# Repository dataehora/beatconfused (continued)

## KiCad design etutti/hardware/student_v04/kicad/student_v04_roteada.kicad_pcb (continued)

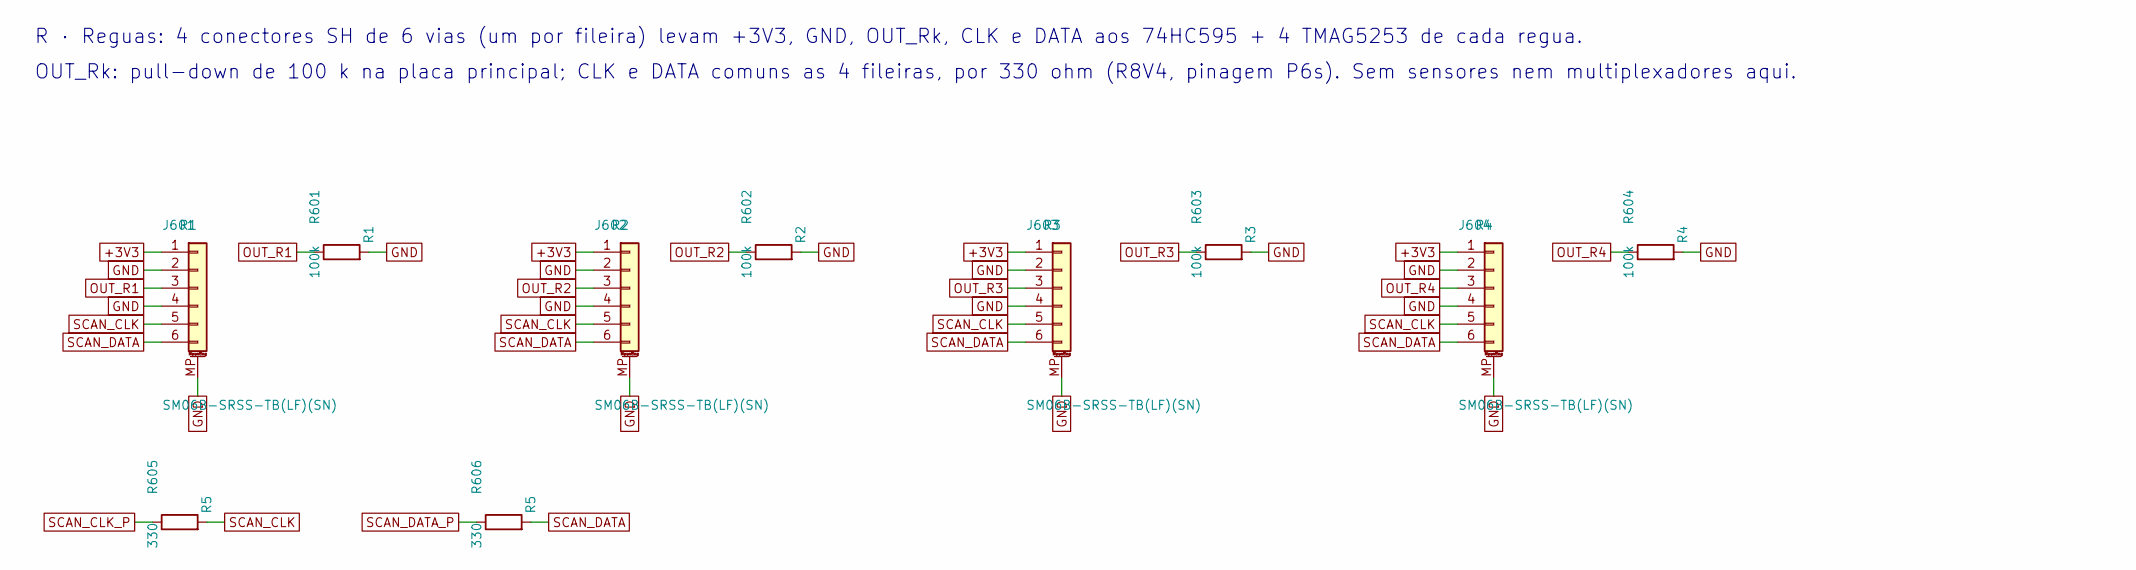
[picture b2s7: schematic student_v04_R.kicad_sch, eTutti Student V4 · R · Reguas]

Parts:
J601, J602, J603, J604: SM06B-SRSS-TB(LF)(SN); JST_SH_SM06B-SRSS-TB_1x06-1MP_P1.00mm_Horizontal; LCSC C160405
R601, R602, R603, R604: 100k; R_0402_1005Metric; LCSC C25741
R605, R606: 330; R_0402_1005Metric; LCSC C25104

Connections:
+3V3: J601.1, J602.1, J603.1, J604.1; also elsewhere on the board
GND: J601.2, J601.4, J601.MP (MountPin), J602.2, J602.4, J602.MP (MountPin), J603.2, J603.4, J603.MP (MountPin), J604.2, J604.4, J604.MP (MountPin), R601.2, R602.2, R603.2, R604.2; also elsewhere on the board
OUT_R1: J601.3, R601.1; also elsewhere on the board
OUT_R2: J602.3, R602.1; also elsewhere on the board
OUT_R3: J603.3, R603.1; also elsewhere on the board
OUT_R4: J604.3, R604.1; also elsewhere on the board
SCAN_CLK: J601.5, J602.5, J603.5, J604.5, R605.2
SCAN_CLK_P: R605.1; also elsewhere on the board
SCAN_DATA: J601.6, J602.6, J603.6, J604.6, R606.2
SCAN_DATA_P: R606.1; also elsewhere on the board

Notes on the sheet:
R · Reguas: 4 conectores SH de 6 vias (um por fileira) levam +3V3, GND, OUT_Rk, CLK e DATA aos 74HC595 + 4 TMAG5253 de cada regua.
OUT_Rk: pull-down de 100 k na placa principal; CLK e DATA comuns as 4 fileiras, por 330 ohm (R8V4, pinagem P6s). Sem sensores nem multiplexadores aqui.

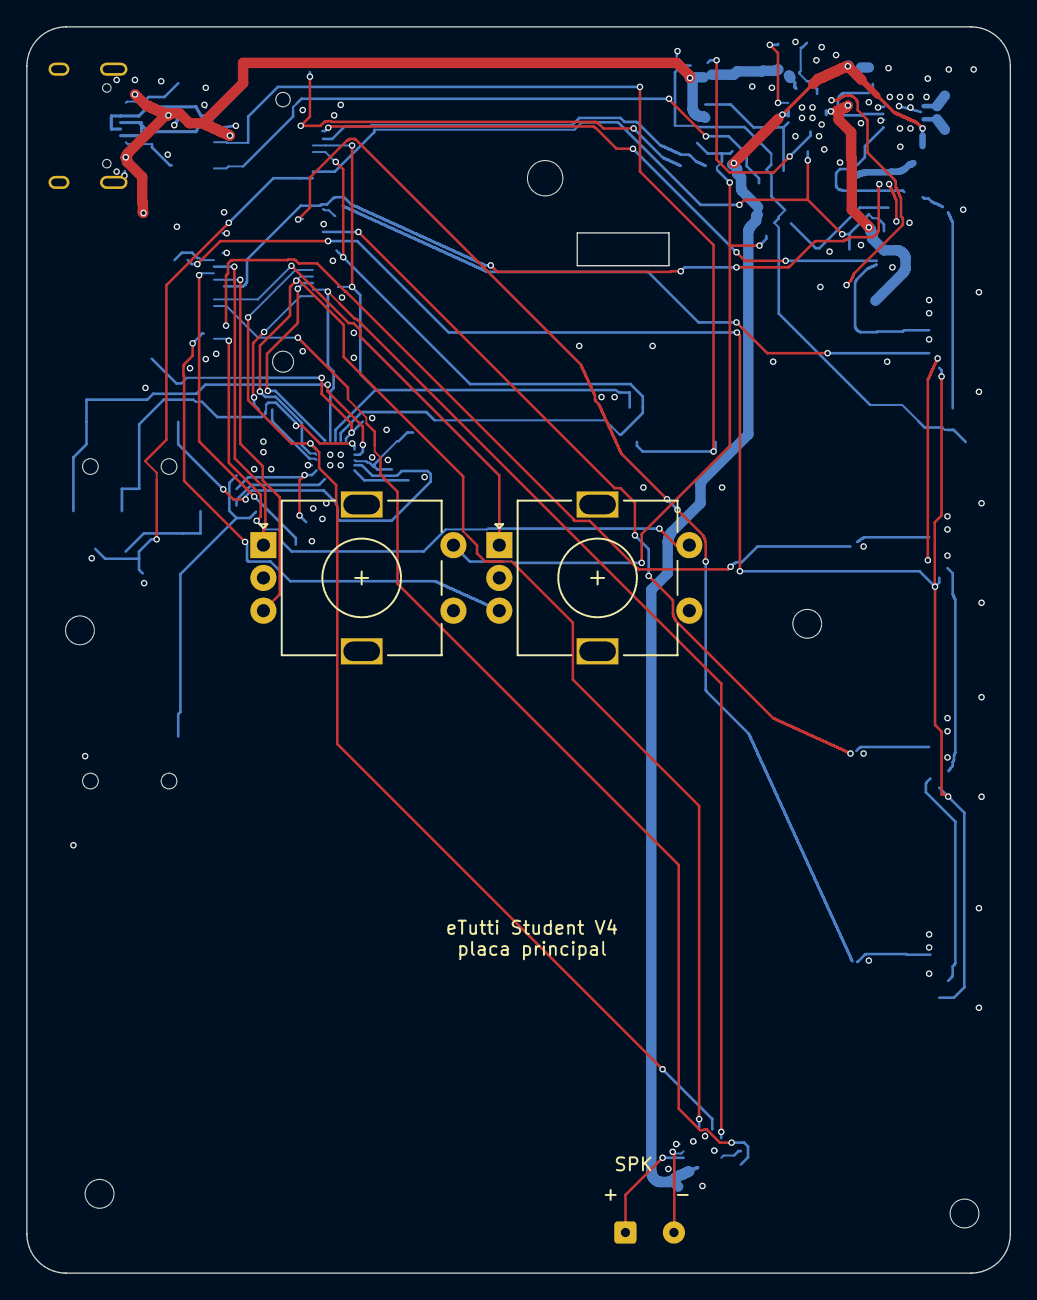
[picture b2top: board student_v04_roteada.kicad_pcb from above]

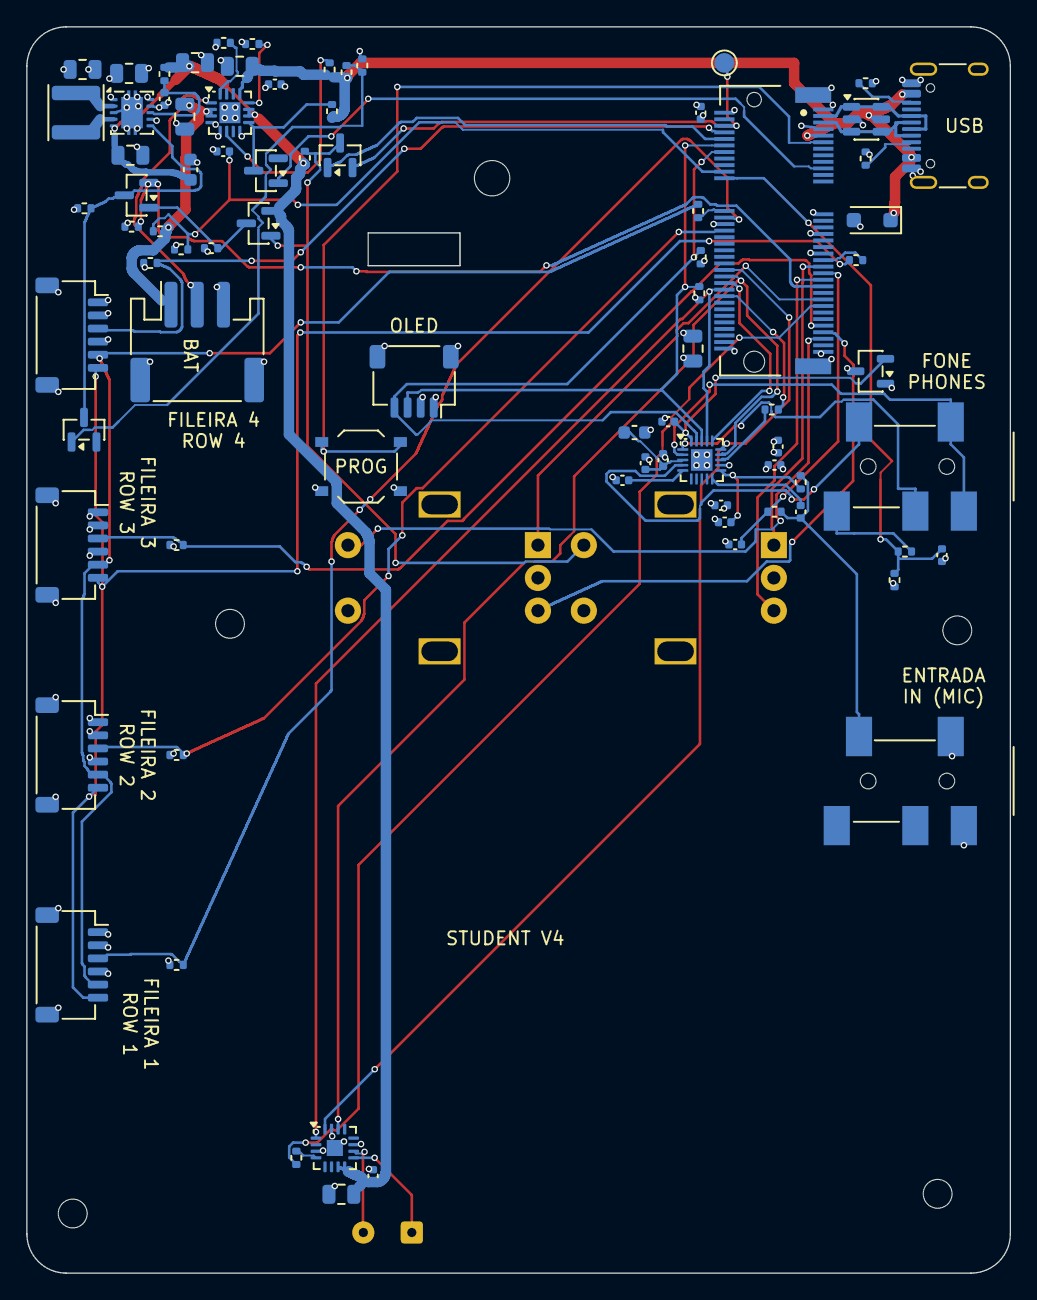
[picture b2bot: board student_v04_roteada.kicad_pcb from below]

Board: 4 copper layers, 75.0 x 95.1 mm, 88 parts (80 on the bottom side), 64 nets.

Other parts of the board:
H1, H2, H3, H4: MountingHole_2.2mm_M2
H101: MountingHole_2.7mm_M2.5

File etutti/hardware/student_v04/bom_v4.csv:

lcsc,valor,classe_jlc,qtd,referencias,preco_unit_usd
C15850,10uF,Basic,8,C101 C201 C202 C203 C206 C207 C208 C501,0.0311
C1525,100nF,Basic,11,C102 C204 C205 C209 C302 C304 C305 C307 C308 C311 C502,0.0025
C19702,10uF,Basic,1,C210,0.0167
C12530,2.2uF,Basic,3,C301 C303 C306,0.005
C52923,1uF,Basic,1,C309,0.0055
C151296,SMF5.0A,Extended,1,D201,0.1144
C68978,BAV70,Basic,4,D202 D203 D206 D205,0.0152
C1002,600R@100MHz,Basic,1,FB301,0.0105
C48985906,91302-42-067RCE,Extended,1,J101,1.2304
C165948,TYPE-C-31-M-12,Extended,1,J201,0.1869
C265101,S3B-PH-SM4-TB,Extended,1,J202,0.2641
C49284723,PJ-327A,Extended,2,J301 J302,0.2194
C160404,SM04B-SRSS-TB(LF)(SN),Extended,1,J401,0.2147
C160405,SM06B-SRSS-TB(LF)(SN),Extended,4,J601 J602 J603 J604,0.8966
C167825,2.2uH,Extended,1,L201,0.0516
C15127,AO3401A,Basic,1,Q203,0.082
C25076,100,Basic,2,R105 R216,0.0011
C25905,5.1k,Basic,2,R201 R202,0.0014
C25879,2.2k,Basic,3,R203 R301 R302,0.0011
C25867,1.5k,Basic,1,R204,0.0029
C25744,10k,Basic,2,R205 R214,0.001
C25741,100k,Basic,11,R206 R210 R211 R213 R215 R303 R306 R601 R602 R603 R604,0.0009
C26083,1M,Basic,5,R208 R209 R212 R304 R501,0.001
C17168,0,Basic,1,R305,0.0012
C25104,330,Basic,2,R605 R606,0.0011
C318884,Program,Basic,1,SW403,0.0212
C7519,USBLC6-2SC6,Extended,1,U201,0.1561
C54313,BQ24074RGTR,Extended,1,U202,2.1646
C28060,TPS63001DRCR,Extended,1,U204,1.6247
C2651833,SGTL5000XNLA3,Extended,1,U301,9.5073
C347373,XC6206P182MR,Extended,1,U302,0.021
C910544,MAX98357AETE+T,Extended,1,U501,1.2451

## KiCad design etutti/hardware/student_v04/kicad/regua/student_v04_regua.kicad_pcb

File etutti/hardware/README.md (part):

# eTuttino — PCB design (Hall-effect, velocity-sensitive)

A 44-key chromatic button-accordion controller (C-griff, G3–E6).

- **Keys:** Gateron magnetic (Hall-effect) switches, MX-compatible.
- **Sensing:** a TI DRV5056A3 linear Hall sensor under every key, so the
  firmware knows how far down each key is, and from how fast it went
  down, the note's velocity.
- **Brain:** a Teensy 4.0 with the PJRC Audio Adaptor Board Rev D stacked
  on it.

The firmware is in [`../firmware`](../firmware), the web page is
[beatconfused.com/etutti](https://beatconfused.com/etutti/), and the case
(Seixo / Madeira, SPEC v9; shape frozen since v7) is in [`case/`](case/).

> **Board v0.7 (this one) is made for the SPEC v7–v9 case.** The keys sit
> on the case's hexagonal grid (18.5 mm pitch), and the board takes the
> case's inner outline. The assembly and user manuals in
> [`../manuais`](../manuais/) describe this board, the case and the
> controls board; their pictures come from
> [`manual3d/`](manual3d/) (Blender). Nothing has been built
> yet: only the firmware has run on a real Teensy + Audio Board.

## Ordering (ready to upload)

Generated, routed and checked: KiCad DRC 0 errors, 0 warnings,
0 unconnected; firmware cross-check 44/44.

| File | Upload it as |
| --- | --- |
| [`fab/etuttino_gerbers.zip`](fab/etuttino_gerbers.zip) | **the PCB**: Gerbers + drill files. 2 layers, FR-4, **1.2 mm**, shaped outline (328 × 97 mm bounding box) |
| [`fab/etuttino_bom.csv`](fab/etuttino_bom.csv) + [`fab/etuttino_cpl_bottom.csv`](fab/etuttino_cpl_bottom.csv) | **assembly** (JLCPCB PCBA, *Bottom Side*): every SMD part is on the back |
| [`fab/etuttino_plate_gerbers.zip`](fab/etuttino_plate_gerbers.zip) | **the switch plate**: a copper-less **1.6 mm** FR-4 board with the 14 mm cutouts, cut to the case's plate outline (the case is drawn for 1.6 since SPEC v8) |
| [`fab/etuttino_controls_gerbers.zip`](fab/etuttino_controls_gerbers.zip) | **the controls board**: 2 layers, FR-4 1.6 mm, 41.5 × 25.5 mm, all through-hole (see below) |
| [`case/out/`](case/out/) | **the case** (STEP + STL) and the button caps; see [`case/README.md`](case/README.md) |

The BOM has LCSC numbers for the JLCPCB basic parts. Match the two TI parts
(`DRV5056A3QDBZR`, `CD74HC4067M96`) by manufacturer part number in
JLCPCB's BOM tool. Check every part's rotation in the placement preview
before paying.

## Why the sensors are on the back

The DRV5056 is unipolar: its output only rises when a **south** pole faces
its marked (top) side. Gateron's magnetic switches have the magnet's
**north** pole facing down, so a sensor on the front, facing up, would read
nothing.

On the back, the sensor faces away from the switch. The field reaches it
through the board from behind, and the sensor reads that as positive. A
1.2 mm board keeps the sensor as close to the magnet as that allows.

The A3 variant (30 mV/mT at 3.3 V, about 80 mT before saturation) leaves
headroom against Gateron's ~10 mT at rest and ~90 mT bottomed out. The A4
also works.

## Source files and regenerating

| File | What it is |
| --- | --- |
| [`case/pcb_envelope.py`](case/pcb_envelope.py) → `case/out/pcb_envelope.json` | the room the case leaves for the board: outline (notched round the case's screw bosses), plate outline, bottom-plate pillars, height levels, key centres, the stack's and J3's places. Run with the CadQuery venv (see `case/README.md`) |
| [`generate.py`](generate.py) | reads that envelope. Single source of the key layout and of the sensor → multiplexer map (plain Python 3). Prints the `KEY_INPUT` table for the firmware |
| [`build_pcb.py`](build_pcb.py) | builds and **routes** the KiCad board inside that outline, runs DRC, checks it against the firmware, exports everything in `fab/` |
| [`controls_pcb.py`](controls_pcb.py) | the controls board: places, routes (the same router), DRCs and exports it |
| [`mechanics.py`](mechanics.py) | how far the board bends under a key press on the case's pillars (KiCad's Python, numpy) |
| [`manual3d/`](manual3d/) | the assembly manual's pictures: photo-like renders and numbered line drawings of every step, made in Blender from the case STLs, both KiCad boards (`kicad-cli` GLB) and a library of datasheet-sized parts (`parts.py`). `build.py` runs it all; the visual standard and the balloon numbers are in [`manual3d/STYLE.md`](manual3d/STYLE.md) |
| [`etuttino.pretty/`](etuttino.pretty) | footprint library: `Gateron_Magnetic_MX_1u` (two 1.75 mm peg holes, no centre post, no pins), origin at the switch centre |
| [`kicad/etuttino.kicad_pcb`](kicad/etuttino.kicad_pcb), [`kicad/etuttino_plate.kicad_pcb`](kicad/etuttino_plate.kicad_pcb) | the routed board and the plate |
| `build/etuttino_pcb_preview.svg`, `build/etuttino_keys.csv`, `build/etuttino_plate.dxf` | preview; each key's switch, sensor, multiplexer channel, Teensy pin, note and X/Y; the plate as DXF (for aluminium) |

After a case change, rebuild in this order:

```bash
C:/Users/julia/.venvs/cadquery/Scripts/python.exe case/case.py
C:/Users/julia/.venvs/cadquery/Scripts/python.exe case/pcb_envelope.py
python generate.py
"C:/Program Files/KiCad/10.0/bin/python.exe" build_pcb.py
"C:/Program Files/KiCad/10.0/bin/python.exe" mechanics.py
```

Each routing attempt takes about four minutes. The router is greedy: if
a net can't be routed, the script starts again with that net first, up to
20 times. `DEFAULT_ROUTE_FIRST` keeps the order that worked
(`OUT_U41,OUT_U42,GND,LED_R,LED_G_DRV,OUT_U34` for v0.6 and v0.7).

`build_pcb.py` exits with an error if any of these happens:

- DRC finds a problem.
- Anything is left unconnected.
- A part on the back sits over one of the bottom plate's pillars.
- A key doesn't reach the multiplexer channel and Teensy pin that the
  firmware's tables give.

It writes the routed channels into the sketch's `KEY_INPUT`.

## Layout

Chromatic accordion, C-griff, on a **hexagonal grid**: every button is
**18.5 mm** from its six neighbours, and the rows are 18.5 × cos 30° =
**16.02 mm** apart.

- Each key along a row is a **minor third (3 semitones)** above the
  previous one. A diagonal step to the next row is **one semitone**.
- Row 4 repeats row 1's notes from A3 to C6, on row 2's columns.
- **Row 1 is nearest the player.** It is at the front edge, which is the
  bottom of KiCad's top view.
- The same switches also play **B-griff**: the web page's C/B-griff
  switch sends CC 24, and the firmware swaps rows 1 and 3. The PCB does
  not change.

| Row | Keys | Notes | y (mm) |
| --- | --- | --- | --- |
| 1 | 11 | A3 C4 D♯4 F♯4 A4 C5 D♯5 F♯5 A5 C6 D♯6 | 74.03 |
| 2 | 12 | G3 A♯3 C♯4 E4 G4 A♯4 C♯5 E5 G5 A♯5 C♯6 E6 | 58.01 |
| 3 | 11 | G♯3 B3 D4 F4 G♯4 B4 D5 F5 G♯5 B5 D6 | 41.99 |
| 4 | 10 | A3 C4 D♯4 F♯4 A4 C5 D♯5 F♯5 A5 C6 | 25.97 |

**Coordinates** are the case SPEC's. x is measured from the case's left
face, y towards the player. That is KiCad's top view as it stands.

**The board** is the case's inner cavity less 0.5 mm, notched round the
nine screw columns. It fits both the Seixo (2.5 mm walls) and the Madeira
(4 mm). On the left it runs under the interface area, where the Teensy +
Audio Board stack sits in the back corner:

- USB faces the case's left face, where a short cable goes to the panel
  socket.
- The VIN row is at the back.
- The stack is ~13 mm tall in the eTuttino and 10 mm or less in the
  eTuttiChorus.
- The Audio Board sits ~3 mm above the PCB on its header legs.
- These positions come from `case/fit_check.py`.

**Held by the case:**

- Under the keys, the lid presses the plate's edge, the plate presses
  the switches, and the switches' bottom housings press the board.
- Under the interface, two M2 screws come up from below. They go through
  the bottom plate's pillars at (30; 60) and (12; 70) and through the
  board's holes H1 and H2, with a nut on top. These two pillars are
  Ø6, with a counterbore for the head. The router keeps copper 3.5 mm
  away from both holes.
- The board rests on **64 pillars** of the bottom plate, one at the
  centre of every triangle of three neighbouring keys (10.7 mm from each
  sensor). The case has 3 more pillars under the interface.
- Under a firm 3 N press the board sags **0.044 mm** at worst (E6, row 2)
  and 0.009 mm on average. Check with `mechanics.py`.
- No part on the back may sit over a pillar. `build_pcb.py` checks this.

## Electrical

**Per key (back side):**

- A DRV5056A3 (SOT-23) straight under the switch centre.
- Its 100 nF capacitor just behind it.
- A 3.3 V bus behind each key row and a GND bus in front of it (0.4 mm).
- The sensor output drops to a via and is routed to its multiplexer.

**Multiplexers:** three CD74HC4067 (SOIC-24), all on the back.

- U51 sits in front of the interface, left of rows 1 and 2. It serves row 1
  and the left end of row 2.
- U52 and U53 lie sideways in the strip behind row 4 and serve the rest,
  split left and right.
- The router picks each key's channel; see `build/etuttino_keys.csv`.
- The address lines are shared, and Enable is tied to GND.

| Net | Teensy pin |
| --- | --- |
| SEL0–SEL3 (multiplexer address S0–S3) | 0, 1, 2, 3 |
| COM0 / COM1 / COM2 (U51 / U52 / U53 output) | 14 (A0) / 15 (A1) / 16 (A2) |
| VIN (USB 5 V) → regulator | VIN |
| GND | GND (both rows) |
| LED_R_DRV / LED_G_DRV → 330 Ω (R1 / R2) → J3 | 4 (red), 5 (green) |
| POT → J3 | 22 (A8) |
| ENC_A / ENC_B / ENC_SW → J3 | 17 / 9 / 6 |

**J3, the controls board.** A JST PH 2.0 mm 8-pin vertical header, in front
of the Audio Board, under the interface lid. A short 1:1 cable goes up
to the controls board.

| Pin | Net |
| --- | --- |
| 1 | VCC 3.3 V |
| 2 | GND |
| 3 | POT |
| 4 | ENC_A |
| 5 | ENC_B |
| 6 | ENC_SW |
| 7 | LED_R |
| 8 | LED_G |

The firmware reads the pot as the volume and the encoder as the
instrument selector (see `../firmware/README.md`). With no controls board
plugged in, the pot input is ignored. Pin 6 is the Audio Board's optional
memory-chip select, so leave that chip unfitted.

## Controls board

`controls_pcb.py` → `kicad/etuttino_controls.kicad_pcb` and
`fab/etuttino_controls_gerbers.zip`. KiCad DRC 0 / 0 / 0. In case
coordinates it spans x 14.5–56, y 35.5–61. It hangs under the interface lid
on two posts of the case, with M2 screws through H1 and H2 from below. Its
top faces the lid:

| Ref | Part | Where |
| --- | --- | --- |
| RV1 | Alps RK09K vertical pot, 10 k linear, 6 mm shaft L = 15 | shaft at (20; 45): volume |
| SW1 | Alps EC11E encoder with push switch, L = 15 | shaft at (37; 45): instrument |
| D1 | 3 mm red/green LED, common cathode | (52; 45), on a spacer up to the lid's hole (Seixo) or just under the light pipe (Madeira); `case/FIT_CHECK.md` gives the spacer length |
| J1 | JST PH B8B-PH-K vertical, on the back, facing down | the cable drops straight to the main board's J3, pin for pin |

The encoder's common and one switch leg go to GND. The Teensy's pull-ups
do the rest. The LED's 330 Ω resistors are on the main board.

**Power LED.** A 3 mm red/green bicolour LED (common cathode) on the
controls board, under the lid's LED hole, or the Madeira's light pipe:

- orange while the keys are read at power-up;
- green while playing;
- blinking red on an error.

**Power.** 44 sensors draw about 260 mA, more than the Teensy's own 3.3 V
pin should give. An AMS1117-3.3 (U60, SOT-223) makes a separate 3.3 V rail
from VIN for the sensors and the multiplexers:

- it sits on the back between the Teensy pin rows;
- it has 10 µF in and 22 µF out.

**Pins kept clear of:**

- 7, 8, 18–21, 23: the Audio Board's audio and I²C;
- 10–13: its SD card;
- 15 is its *optional* volume pot, which is not fitted on a stock board, so
  COM1 can use it.

**Routing:** two layers.

- Per-key wiring and the row buses are laid deterministically.
- Everything else goes through a small A* grid router in `build_pcb.py`:
  0.254 mm grid aligned to the Teensy pins, both layers, vias, KiCad's
  clearances, 0.5 mm from the board's outline.
- KiCad's DRC then checks the result independently.

## Teensy + Audio Board mounting

- Two rows of 14 holes (2.54 mm pitch, 15.24 mm apart), with the 0–12 row
  at the front and the VIN–13 row at the back. The silkscreen marks
  "GND"/"0", "VIN"/"23" and "< USB".
- Two 1×14 extra-long male headers (≈ 20–25 mm pins) join all three
  boards: the Teensy is soldered straight onto the Audio Board, the
  header's plastic as the only spacer, and the long legs go on down
  through these holes with the Audio Board ~3 mm above the PCB, soldered
  and trimmed on the back.
- Stack height, from under the Audio Board to the top of the Teensy's
  USB: the case was checked with 13 mm and has room for 16.9 mm (Seixo) /
  16.4 mm (Madeira); the eTuttiChorus needs 10 mm or less, to clear the
  screen.
- USB goes to the panel socket through a short cable with a 90° micro-USB
  plug. The panel headphone jack is wired to the Audio Board's headphone
  pads.

## Bill of materials (main board)

| Qty | Part | Notes |
| --- | --- | --- |
| 44 | Gateron KS-20 magnetic switch (north pole down) | plate-mounted, **not soldered**: no pins, two plastic pegs |
| 44 | DRV5056A3QDBZR, SOT-23 | back, under each switch |
| 47 | 100 nF 0805 | one per sensor + one per multiplexer |
| 3 | CD74HC4067M96, SOIC-24 | back |
| 1 | AMS1117-3.3, SOT-223 | back |
| 1 + 1 | 10 µF, 22 µF 0805 | regulator input / output |
| 2 | 330 Ω 0805 | LED resistors R1, R2 (back) |
| 1 | JST PH 8-pin vertical header (B8B-PH-K-S) + a 1:1 PH cable, ~60 mm | J3, to the controls board |
| 2 + 2 | M2 × 10 mm screw + M2 nut | through the bottom plate's two thick pillars and H1 / H2 |
| 1 | Teensy 4.0 + PJRC Audio Adaptor Board **Rev D** | + 2 × 1×14 extra-long male headers |
| 1 | switch plate | 1.6 mm FR-4 from `fab/etuttino_plate_gerbers.zip`, or 1.5 mm aluminium from `build/etuttino_plate.dxf` |
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
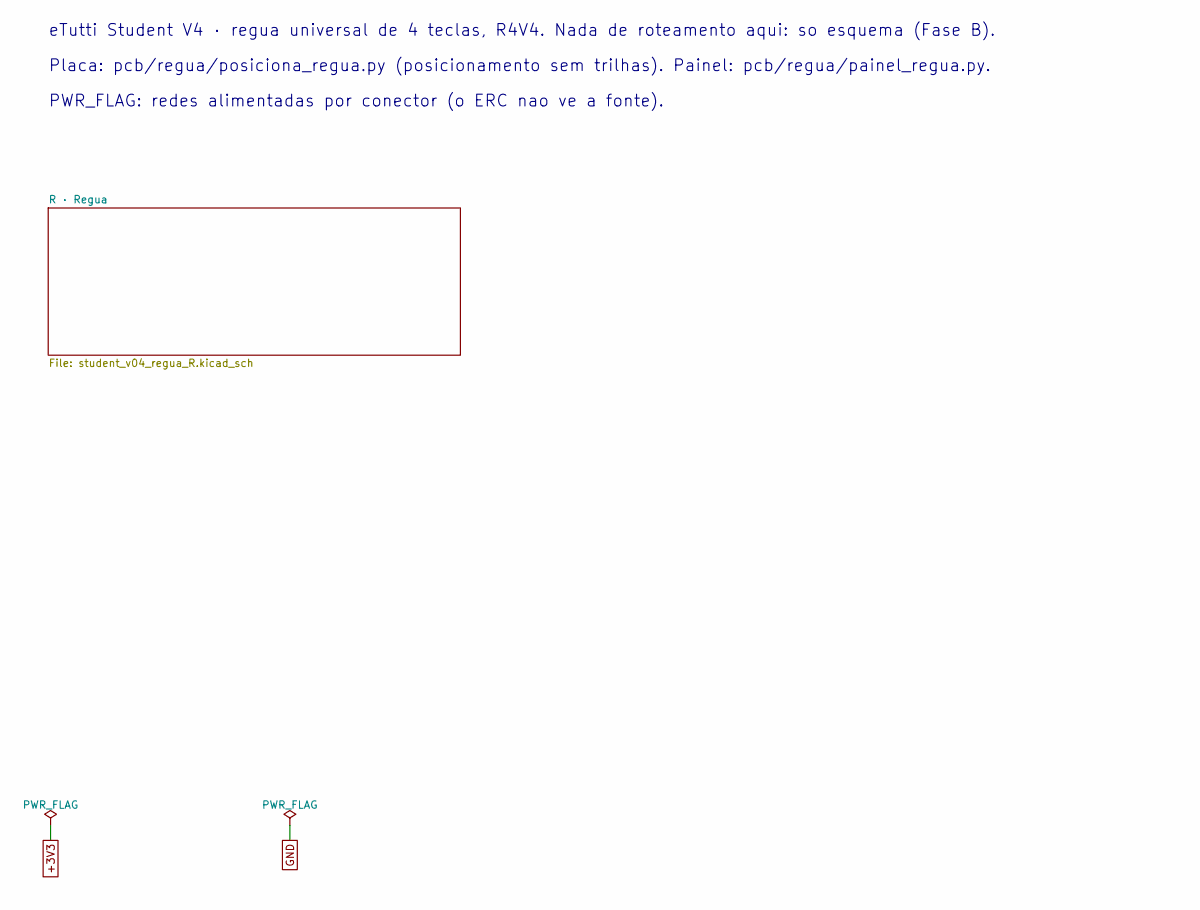
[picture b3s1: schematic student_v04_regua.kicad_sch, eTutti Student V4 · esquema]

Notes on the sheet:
eTutti Student V4 · regua universal de 4 teclas, R4V4. Nada de roteamento aqui: so esquema (Fase B).
Placa: pcb/regua/posiciona_regua.py (posicionamento sem trilhas). Painel: pcb/regua/painel_regua.py.
PWR_FLAG: redes alimentadas por conector (o ERC nao ve a fonte).

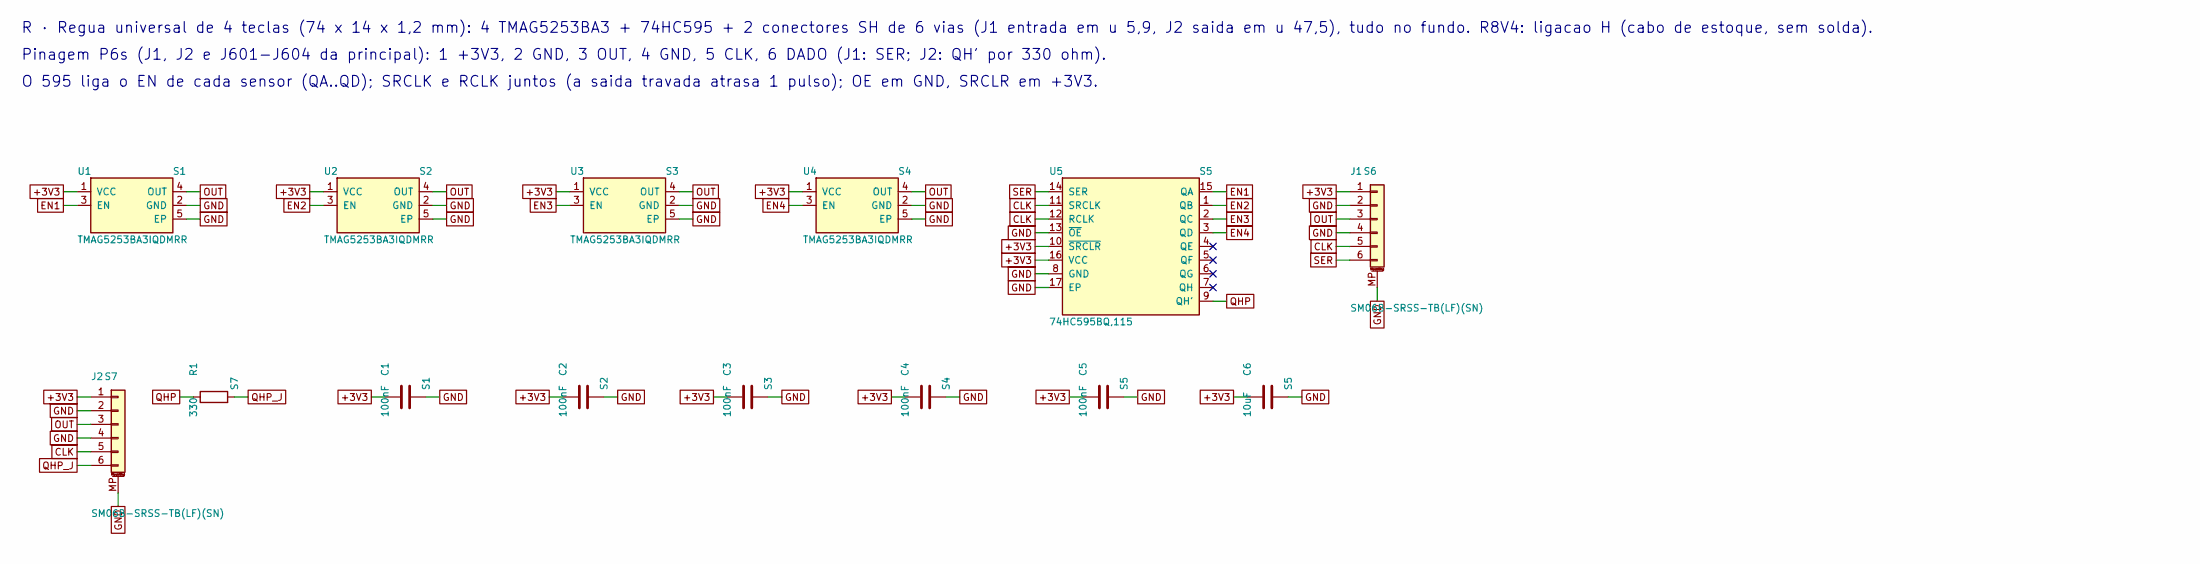
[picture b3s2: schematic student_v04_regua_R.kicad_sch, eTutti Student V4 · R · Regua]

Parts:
C1, C2, C3, C4, C5: 100nF; C_0402_1005Metric; LCSC C1525
C6: 10uF; C_0805_2012Metric; LCSC C15850
J1, J2: SM06B-SRSS-TB(LF)(SN); JST_SH_SM06B-SRSS-TB_1x06-1MP_P1.00mm_Horizontal; LCSC C160405
R1: 330; R_0402_1005Metric; LCSC C25104
U1, U2, U3, U4: TMAG5253BA3IQDMRR; Texas_X2SON-4-1EP_1.1x1.4mm_P0.5mm_EP0.8x0.6mm; LCSC C22401868
U5: 74HC595BQ,115; DHVQFN-16-1EP_2.5x3.5mm_P0.5mm_EP1x2mm; LCSC C730243

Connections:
+3V3: C1.1, C2.1, C3.1, C4.1, C5.1, C6.1, J1.1, J2.1, U1.1 (VCC), U2.1 (VCC), U3.1 (VCC), U4.1 (VCC), U5.10 (~SRCLR), U5.16 (VCC)
CLK: J1.5, J2.5, U5.11 (SRCLK), U5.12 (RCLK)
EN1: U1.3 (EN), U5.15 (QA)
EN2: U2.3 (EN), U5.1 (QB)
EN3: U3.3 (EN), U5.2 (QC)
EN4: U4.3 (EN), U5.3 (QD)
GND: C1.2, C2.2, C3.2, C4.2, C5.2, C6.2, J1.2, J1.4, J1.MP (MountPin), J2.2, J2.4, J2.MP (MountPin), U1.2 (GND), U1.5 (EP), U2.2 (GND), U2.5 (EP), U3.2 (GND), U3.5 (EP), U4.2 (GND), U4.5 (EP), U5.8 (GND), U5.13 (~OE), U5.17 (EP)
OUT: J1.3, J2.3, U1.4 (OUT), U2.4 (OUT), U3.4 (OUT), U4.4 (OUT)
QHP: R1.1, U5.9 (QH')
QHP_J: J2.6, R1.2
SER: J1.6, U5.14 (SER)

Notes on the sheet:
R · Regua universal de 4 teclas (74 x 14 x 1,2 mm): 4 TMAG5253BA3 + 74HC595 + 2 conectores SH de 6 vias (J1 entrada em u 5,9, J2 saida em u 47,5), tudo no fundo. R8V4: ligacao H (cabo de estoque, sem solda).
Pinagem P6s (J1, J2 e J601-J604 da principal): 1 +3V3, 2 GND, 3 OUT, 4 GND, 5 CLK, 6 DADO (J1: SER; J2: QH' por 330 ohm).
O 595 liga o EN de cada sensor (QA..QD); SRCLK e RCLK juntos (a saida travada atrasa 1 pulso); OE em GND, SRCLR em +3V3.

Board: 4 copper layers, 25 parts (14 on the bottom side), 11 nets, no tracks yet.

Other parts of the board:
H1, H2, H3: MountingHole_2.2mm_M2
PEG1a, PEG1b, PEG2a, PEG2b, PEG3a, PEG3b, PEG4a, PEG4b: MountingHole_2.2mm_M2

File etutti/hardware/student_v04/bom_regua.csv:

lcsc,valor,classe_jlc,qtd,referencias,preco_unit_usd_est
C1525,100nF,Basic,5,C1 C2 C3 C4 C5,0.001
C15850,10uF,Basic,1,C6,0.008
C160405,SM06B-SRSS-TB(LF)(SN),Extended,2,J1 J2,0.8966
C25104,330,Basic,1,R1,0.001
C22401868,TMAG5253BA3IQDMRR,Extended,4,U1 U2 U3 U4,0.600
C730243,"74HC595BQ,115",Extended,1,U5,0.176

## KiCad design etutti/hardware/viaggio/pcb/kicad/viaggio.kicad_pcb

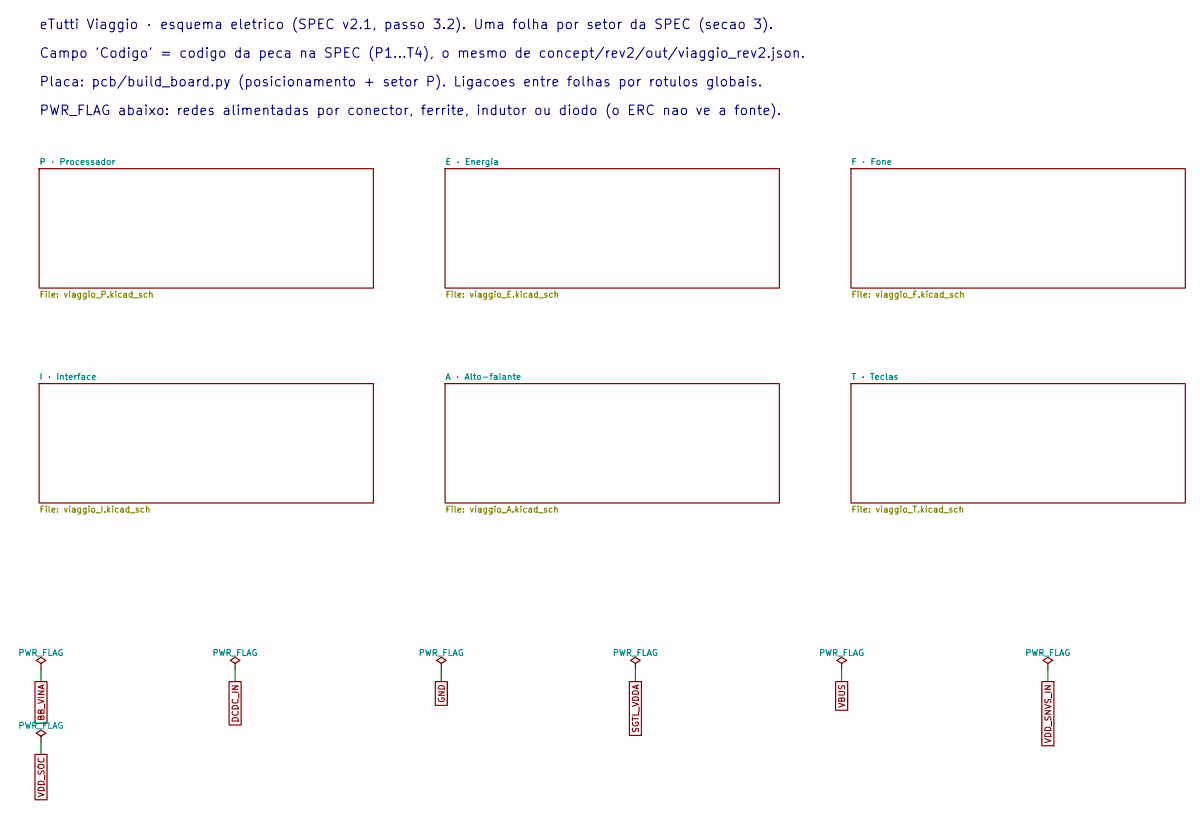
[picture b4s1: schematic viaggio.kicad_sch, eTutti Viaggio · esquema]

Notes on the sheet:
eTutti Viaggio · esquema eletrico (SPEC v2.1, passo 3.2). Uma folha por setor da SPEC (secao 3).
Campo 'Codigo' = codigo da peca na SPEC (P1...T4), o mesmo de concept/rev2/out/viaggio_rev2.json.
Placa: pcb/build_board.py (posicionamento + setor P). Ligacoes entre folhas por rotulos globais.
PWR_FLAG abaixo: redes alimentadas por conector, ferrite, indutor ou diodo (o ERC nao ve a fonte).

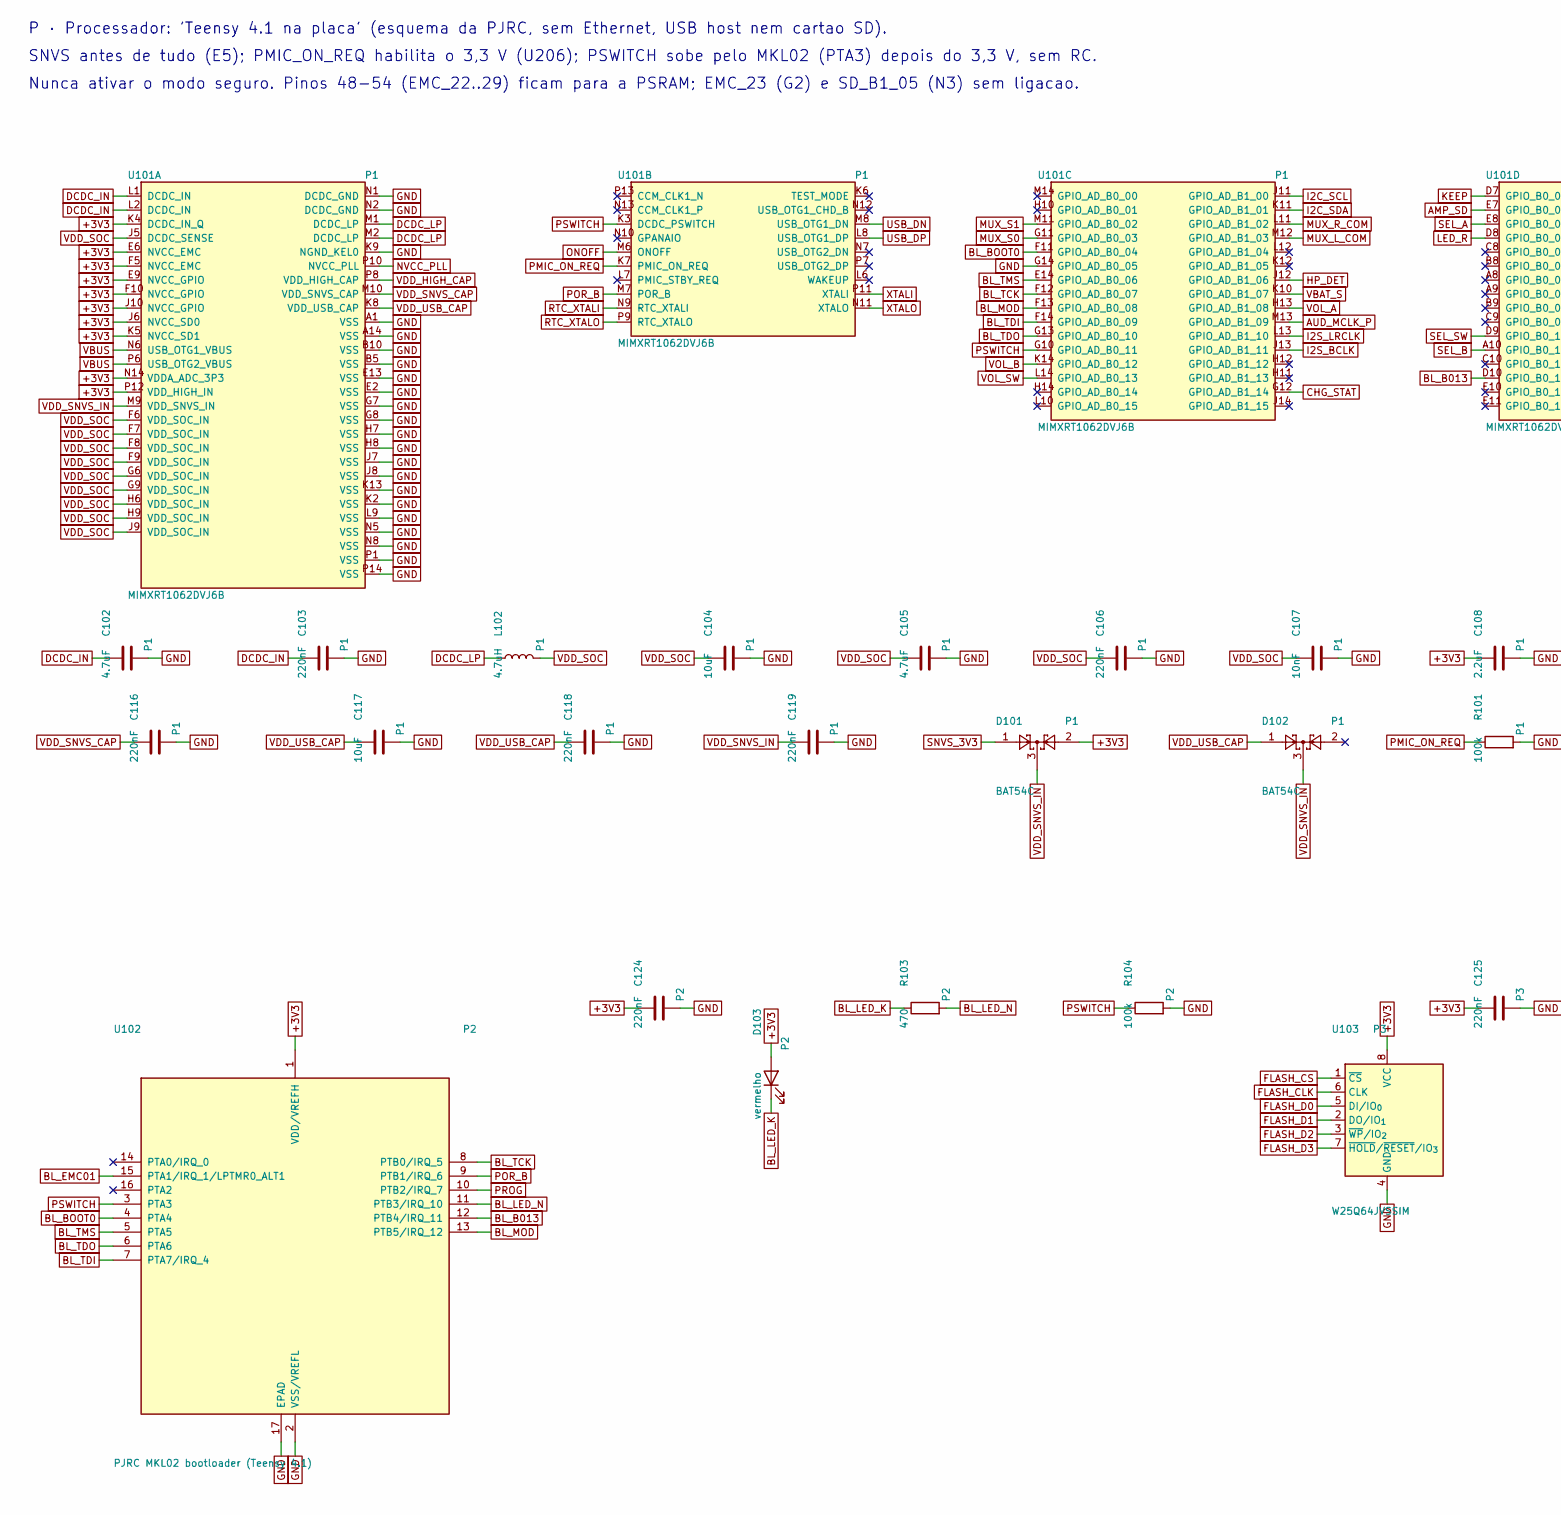
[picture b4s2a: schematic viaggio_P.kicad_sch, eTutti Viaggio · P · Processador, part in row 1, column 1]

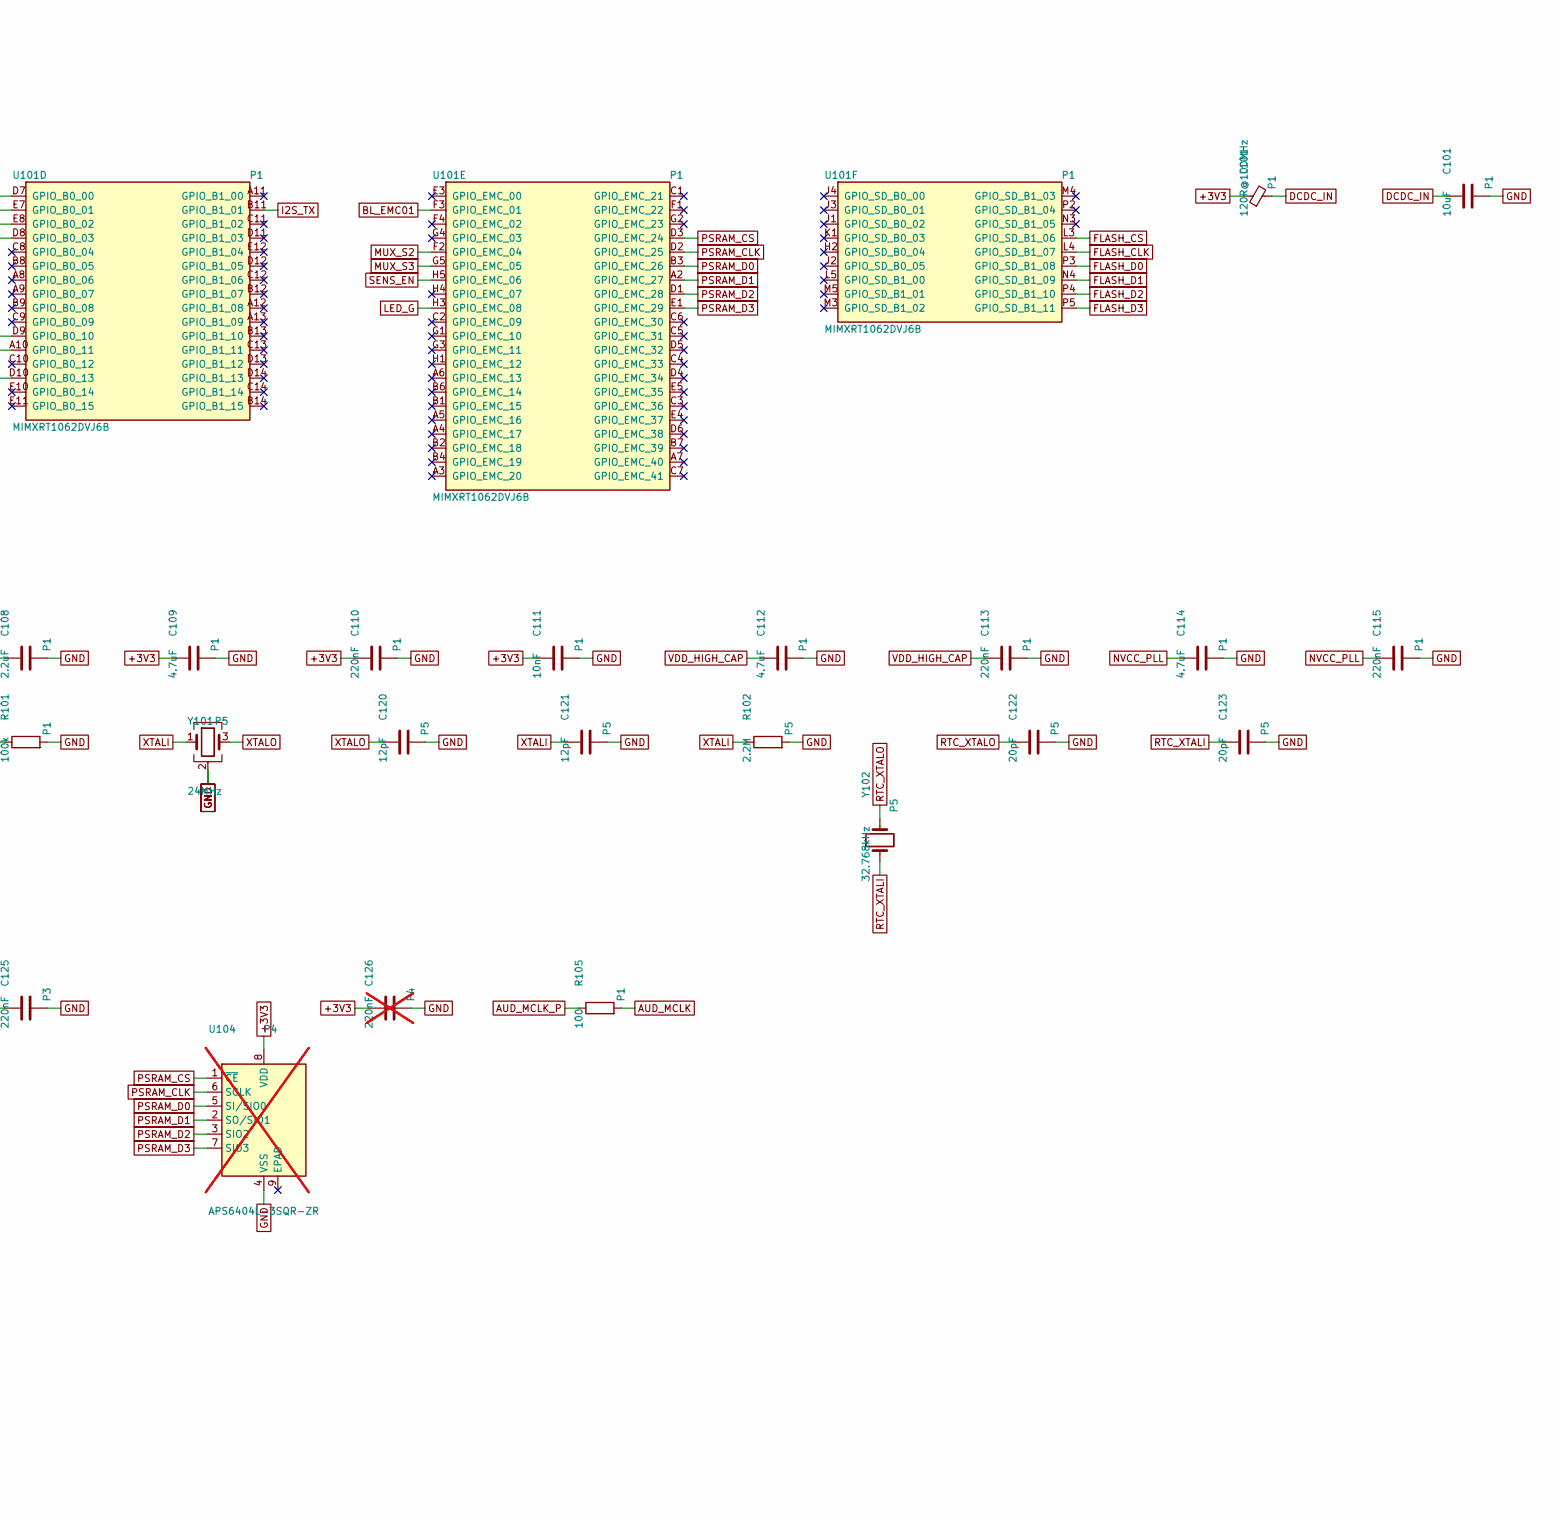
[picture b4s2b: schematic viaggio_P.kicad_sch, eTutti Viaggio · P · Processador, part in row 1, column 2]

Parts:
C101, C104: 10uF; C_0603_1608Metric; LCSC C19702
C102, C105: 4.7uF; C_0603_1608Metric; LCSC C19666
C103, C106, C110, C113, C115, C116, C118, C119, C124, C125: 220nF; C_0402_1005Metric; LCSC C16772
C107, C111: 10nF; C_0402_1005Metric; LCSC C15195
C108: 2.2uF; C_0402_1005Metric; LCSC C12530
C109, C112, C114: 4.7uF; C_0402_1005Metric; LCSC C23733
C117: 10uF; C_0402_1005Metric; LCSC C15525
C120, C121: 12pF; C_0402_1005Metric; LCSC C1547
C122, C123: 20pF; C_0402_1005Metric; LCSC C1554
C126: 220nF; C_0402_1005Metric; LCSC C16772; not fitted
D101, D102: BAT54C; SOT-23; LCSC C134405
D103: vermelho; LED_0603_1608Metric; LCSC C2286
L101: 120R@100MHz; L_0603_1608Metric
L102: 4.7uH; L_0805_2012Metric
R101, R104: 100k; R_0402_1005Metric; LCSC C25741
R102: 2.2M; R_0402_1005Metric
R103: 470; R_0402_1005Metric; LCSC C25117
R105: 100; R_0402_1005Metric; LCSC C25076
U101: MIMXRT1062DVJ6B; BGA-196_12x12mm_P0.8mm_RT1062
U102: PJRC MKL02 bootloader (Teensy 4.1); QFN-16-1EP_3x3mm_P0.5mm_EP1.9x1.9mm
U103: W25Q64JVSSIM; SOIC-8_5.3x5.3mm_P1.27mm; LCSC C5362615
U104: APS6404L-3SQR-ZR; Winbond_USON-8-1EP_3x2mm_P0.5mm_EP0.2x1.6mm; LCSC C3040877; not fitted
Y101: 24MHz; Crystal_SMD_3225-4Pin_3.2x2.5mm; LCSC C431156
Y102: 32.768kHz; Crystal_SMD_3215-2Pin_3.2x1.5mm; LCSC C32346

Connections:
+3V3: C108.1, C109.1, C110.1, C111.1, C124.1, C125.1, C126.1, D101.2, D103.2 (A), L101.1, U101.E6 (NVCC_EMC), U101.E9 (NVCC_GPIO), U101.F5 (NVCC_EMC), U101.F10 (NVCC_GPIO), U101.J6 (NVCC_SD0), U101.J10 (NVCC_GPIO), U101.K4 (DCDC_IN_Q), U101.K5 (NVCC_SD1), U101.N14 (VDDA_ADC_3P3), U101.P12 (VDD_HIGH_IN), U102.1 (VDD/VREFH), U103.8 (VCC), U104.8 (VDD); also elsewhere on the board
AMP_SD: U101.E7 (GPIO_B0_01); also elsewhere on the board
AUD_MCLK: R105.2; also elsewhere on the board
AUD_MCLK_P: R105.1, U101.M13 (GPIO_AD_B1_09)
BL_B013: U101.D10 (GPIO_B0_13), U102.12 (PTB4/IRQ_11)
BL_BOOT0: U101.F11 (GPIO_AD_B0_04), U102.4 (PTA4)
BL_EMC01: U101.F3 (GPIO_EMC_01), U102.15 (PTA1/IRQ_1/LPTMR0_ALT1)
BL_LED_K: D103.1 (K), R103.1
BL_LED_N: R103.2, U102.11 (PTB3/IRQ_10)
BL_MOD: U101.F13 (GPIO_AD_B0_08), U102.13 (PTB5/IRQ_12)
BL_TCK: U101.F12 (GPIO_AD_B0_07), U102.8 (PTB0/IRQ_5)
BL_TDI: U101.F14 (GPIO_AD_B0_09), U102.7 (PTA7/IRQ_4)
BL_TDO: U101.G13 (GPIO_AD_B0_10), U102.6 (PTA6)
BL_TMS: U101.E14 (GPIO_AD_B0_06), U102.5 (PTA5)
CHG_STAT: U101.G12 (GPIO_AD_B1_14); also elsewhere on the board
DCDC_IN: C101.1, C102.1, C103.1, L101.2, U101.L1 (DCDC_IN), U101.L2 (DCDC_IN)
DCDC_LP: L102.1, U101.M1 (DCDC_LP), U101.M2 (DCDC_LP)
FLASH_CLK: U101.L4 (GPIO_SD_B1_07), U103.6 (CLK)
FLASH_CS: U101.L3 (GPIO_SD_B1_06), U103.1 (~CS)
FLASH_D0: U101.P3 (GPIO_SD_B1_08), U103.5 (DI/IO_{0})
FLASH_D1: U101.N4 (GPIO_SD_B1_09), U103.2 (DO/IO_{1})
FLASH_D2: U101.P4 (GPIO_SD_B1_10), U103.3 (~WP/IO_{2})
FLASH_D3: U101.P5 (GPIO_SD_B1_11), U103.7 (~HOLD/~RESET/IO_{3})
GND: C101.2, C102.2, C103.2, C104.2, C105.2, C106.2, C107.2, C108.2, C109.2, C110.2, C111.2, C112.2, C113.2, C114.2, C115.2, C116.2, C117.2, C118.2, C119.2, C120.2, C121.2, C122.2, C123.2, C124.2, C125.2, C126.2, R101.2, R102.2, R104.2, U101.A1 (VSS), U101.A14 (VSS), U101.B5 (VSS), U101.B10 (VSS), U101.E2 (VSS), U101.E13 (VSS), U101.G7 (VSS), U101.G8 (VSS), U101.G14 (GPIO_AD_B0_05), U101.H7 (VSS), U101.H8 (VSS), U101.J7 (VSS), U101.J8 (VSS), U101.K2 (VSS), U101.K9 (NGND_KEL0), U101.K13 (VSS), U101.L9 (VSS), U101.N1 (DCDC_GND), U101.N2 (DCDC_GND), U101.N5 (VSS), U101.N8 (VSS), U101.P1 (VSS), U101.P14 (VSS), U102.2 (VSS/VREFL), U102.17 (EPAD), U103.4 (GND), U104.4 (VSS), Y101.2 (G), Y101.4 (G); also elsewhere on the board
HP_DET: U101.J12 (GPIO_AD_B1_06); also elsewhere on the board
I2C_SCL: U101.J11 (GPIO_AD_B1_00); also elsewhere on the board
I2C_SDA: U101.K11 (GPIO_AD_B1_01); also elsewhere on the board
I2S_BCLK: U101.J13 (GPIO_AD_B1_11); also elsewhere on the board
I2S_LRCLK: U101.L13 (GPIO_AD_B1_10); also elsewhere on the board
I2S_TX: U101.B11 (GPIO_B1_01); also elsewhere on the board
KEEP: U101.D7 (GPIO_B0_00); also elsewhere on the board
LED_G: U101.H3 (GPIO_EMC_08); also elsewhere on the board
LED_R: U101.D8 (GPIO_B0_03); also elsewhere on the board
MUX_L_COM: U101.M12 (GPIO_AD_B1_03); also elsewhere on the board
MUX_R_COM: U101.L11 (GPIO_AD_B1_02); also elsewhere on the board
MUX_S0: U101.G11 (GPIO_AD_B0_03); also elsewhere on the board
MUX_S1: U101.M11 (GPIO_AD_B0_02); also elsewhere on the board
MUX_S2: U101.F2 (GPIO_EMC_04); also elsewhere on the board
MUX_S3: U101.G5 (GPIO_EMC_05); also elsewhere on the board
NVCC_PLL: C114.1, C115.1, U101.P10 (NVCC_PLL)
ONOFF: U101.M6 (ONOFF); also elsewhere on the board
PMIC_ON_REQ: R101.1, U101.K7 (PMIC_ON_REQ); also elsewhere on the board
POR_B: U101.M7 (POR_B), U102.9 (PTB1/IRQ_6)
PROG: U102.10 (PTB2/IRQ_7); also elsewhere on the board
PSRAM_CLK: U101.D2 (GPIO_EMC_25), U104.6 (SCLK)
PSRAM_CS: U101.D3 (GPIO_EMC_24), U104.1 (~CE)
PSRAM_D0: U101.B3 (GPIO_EMC_26), U104.5 (SI/SIO0)
PSRAM_D1: U101.A2 (GPIO_EMC_27), U104.2 (SO/SIO1)
PSRAM_D2: U101.D1 (GPIO_EMC_28), U104.3 (SIO2)
PSRAM_D3: U101.E1 (GPIO_EMC_29), U104.7 (SIO3)
PSWITCH: R104.1, U101.G10 (GPIO_AD_B0_11), U101.K3 (DCDC_PSWITCH), U102.3 (PTA3)
RTC_XTALI: C123.1, U101.N9 (RTC_XTALI), Y102.1
RTC_XTALO: C122.1, U101.P9 (RTC_XTALO), Y102.2
SEL_A: U101.E8 (GPIO_B0_02); also elsewhere on the board
SEL_B: U101.A10 (GPIO_B0_11); also elsewhere on the board
SEL_SW: U101.D9 (GPIO_B0_10); also elsewhere on the board
SENS_EN: U101.H5 (GPIO_EMC_06); also elsewhere on the board
SNVS_3V3: D101.1; also elsewhere on the board
USB_DN: U101.M8 (USB_OTG1_DN); also elsewhere on the board
USB_DP: U101.L8 (USB_OTG1_DP); also elsewhere on the board
VBAT_S: U101.K10 (GPIO_AD_B1_07); also elsewhere on the board
VBUS: U101.N6 (USB_OTG1_VBUS), U101.P6 (USB_OTG2_VBUS); also elsewhere on the board
VDD_HIGH_CAP: C112.1, C113.1, U101.P8 (VDD_HIGH_CAP)
VDD_SNVS_CAP: C116.1, U101.M10 (VDD_SNVS_CAP)
VDD_SNVS_IN: C119.1, D101.3, D102.3, U101.M9 (VDD_SNVS_IN)
VDD_SOC: C104.1, C105.1, C106.1, C107.1, L102.2, U101.F6 (VDD_SOC_IN), U101.F7 (VDD_SOC_IN), U101.F8 (VDD_SOC_IN), U101.F9 (VDD_SOC_IN), U101.G6 (VDD_SOC_IN), U101.G9 (VDD_SOC_IN), U101.H6 (VDD_SOC_IN), U101.H9 (VDD_SOC_IN), U101.J5 (DCDC_SENSE), U101.J9 (VDD_SOC_IN)
VDD_USB_CAP: C117.1, C118.1, D102.1, U101.K8 (VDD_USB_CAP)
VOL_A: U101.H13 (GPIO_AD_B1_08); also elsewhere on the board
VOL_B: U101.K14 (GPIO_AD_B0_12); also elsewhere on the board
VOL_SW: U101.L14 (GPIO_AD_B0_13); also elsewhere on the board
XTALI: C121.1, R102.1, U101.P11 (XTALI), Y101.1
XTALO: C120.1, U101.N11 (XTALO), Y101.3

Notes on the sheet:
P · Processador: 'Teensy 4.1 na placa' (esquema da PJRC, sem Ethernet, USB host nem cartao SD).
SNVS antes de tudo (E5); PMIC_ON_REQ habilita o 3,3 V (U206); PSWITCH sobe pelo MKL02 (PTA3) depois do 3,3 V, sem RC.
Nunca ativar o modo seguro. Pinos 48-54 (EMC_22..29) ficam para a PSRAM; EMC_23 (G2) e SD_B1_05 (N3) sem ligacao.
